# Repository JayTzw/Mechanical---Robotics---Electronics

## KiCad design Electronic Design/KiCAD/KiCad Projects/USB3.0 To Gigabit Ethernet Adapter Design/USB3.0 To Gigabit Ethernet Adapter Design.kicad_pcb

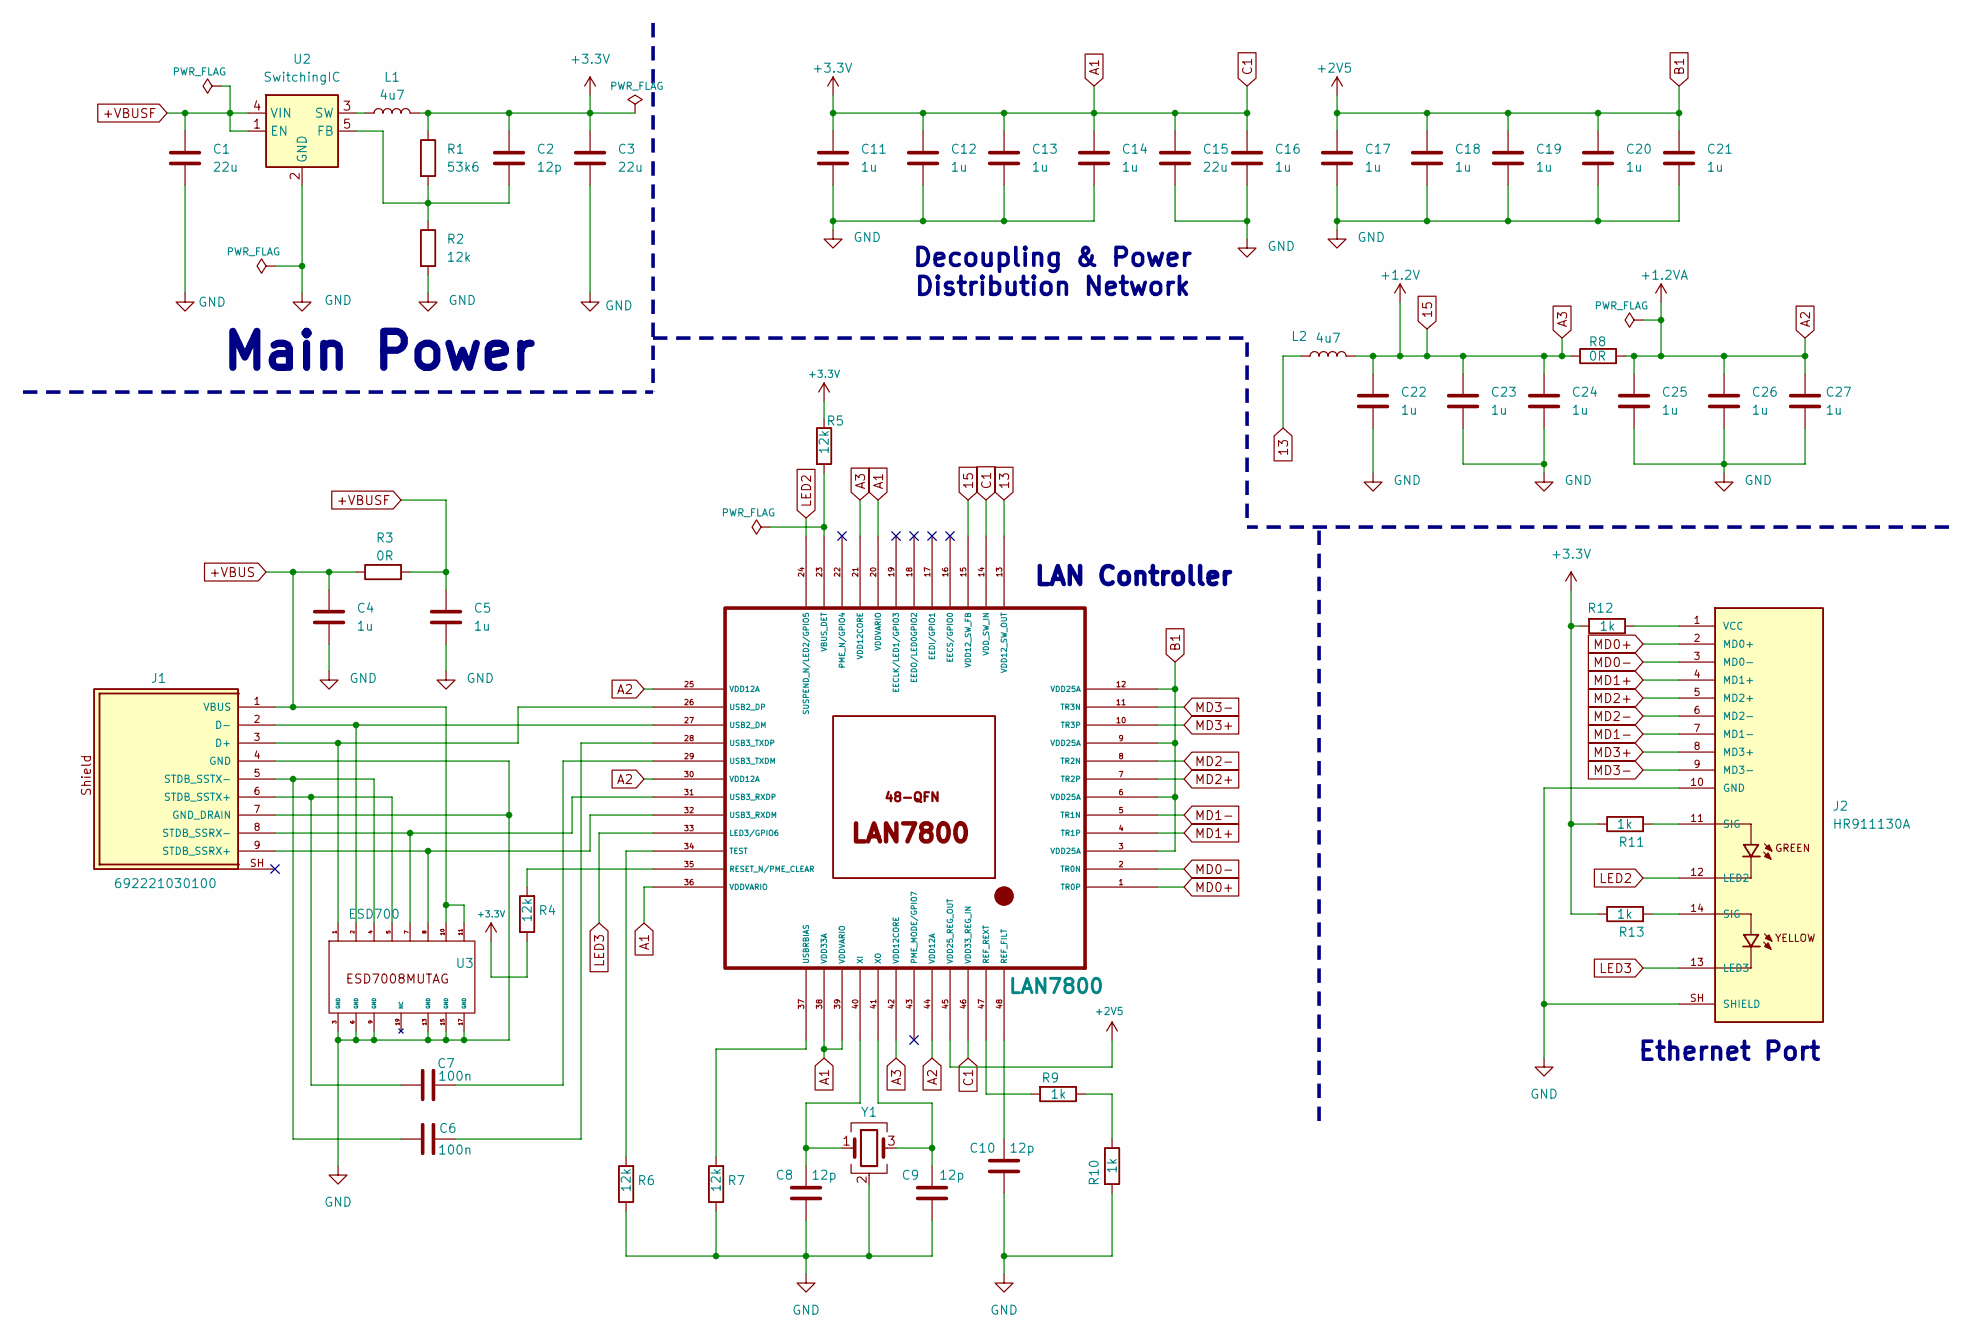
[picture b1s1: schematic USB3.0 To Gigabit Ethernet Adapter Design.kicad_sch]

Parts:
C1, C3, C15: 22u; C_0402_1005Metric
C2, C8, C9, C10: 12p; C_0402_1005Metric
C4, C5, C11, C12, C13, C14, C16, C17, C18, C19, C20, C21, C22, C23, C24, C25, C26, C27: 1u; C_0402_1005Metric
C6, C7: 100n; C_0402_1005Metric
J1: 692221030100
J2: HR911130A; HANRUN_HR911130A; PARTREV A
L1, L2: 4u7; C_0402_1005Metric
R1: 53k6; R_0402_1005Metric
R2, R4, R5, R6, R7: 12k; R_0402_1005Metric
R3, R8: 0R; R_0402_1005Metric
R9, R10, R11, R12, R13: 1k; R_0402_1005Metric
U1: LAN7800; QFN-48-1EP_7x7mm_P0.5mm_EP5.7x5.7mm_ThermalVias
U2: SwitchingIC; SOT-23-5
U3: ESD700; DIO_MG2040MUTAG
Y1: Crystal_GND24; Crystal_SMD_SeikoEpson_FA238-4Pin_3.2x2.5mm

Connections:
13: L2.1, U1.13 (VDD12_SW_OUT)
15: C22.1, C23.1, C24.1, L2.2, R8.1, U1.15 (VDD12_SW_FB), U1.21 (VDD12CORE), U1.42 (VDD12CORE)
+VBUS: C4.1, J1.1 (VBUS), R3.1, U3.10, U3.11
+VBUSF: C1.1, C5.1, R3.2, U2.1 (EN), U2.4 (VIN)
A1: C2.1, C3.1, C11.1, C12.1, C13.1, C14.1, C15.1, C16.1, L1.2, R1.1, R4.1, R5.1, R11.1, R12.2, R13.1, U1.14 (VDD_SW_IN), U1.20 (VDDVARIO), U1.36 (VDDVARIO), U1.38 (VDD33A), U1.39 (VDDVARIO), U1.46 (VDD33_REG_IN)
A2: C25.1, C26.1, C27.1, R8.2, U1.25 (VDD12A), U1.30 (VDD12A), U1.44 (VDD12A)
B1: C17.1, C18.1, C19.1, C20.1, C21.1, U1.3 (VDD25A), U1.6 (VDD25A), U1.9 (VDD25A), U1.12 (VDD25A), U1.45 (VDD25_REG_OUT)
GND: C1.2, C3.2, C4.2, C5.2, C8.1, C9.1, C10.1, C11.2, C12.2, C13.2, C14.2, C15.2, C16.2, C17.2, C18.2, C19.2, C20.2, C21.2, C22.2, C23.2, C24.2, C25.2, C26.2, C27.2, J1.4 (GND), J1.7 (GND_DRAIN), J2.10 (GND), J2.S2 (SHIELD), J2.SH (SHIELD), R2.2, R6.1, R7.1, R10.2, U2.2 (GND), U3.3 (GND), U3.6 (GND), U3.9 (GND), U3.13 (GND), U3.15 (GND), U3.17 (GND), Y1.2 (G), Y1.4 (G)
LED2: J2.12 (LED2), U1.24 (SUSPEND_N/LED2/GPIO5)
LED3: J2.13 (LED3), U1.33 (LED3/GPIO6)
MD0+: J2.2 (MD0+), U1.1 (TR0P)
MD0-: J2.3 (MD0-), U1.2 (TR0N)
MD1+: J2.4 (MD1+), U1.4 (TR1P)
MD1-: J2.7 (MD1-), U1.5 (TR1N)
MD2+: J2.5 (MD2+), U1.7 (TR2P)
MD2-: J2.6 (MD2-), U1.8 (TR2N)
MD3+: J2.8 (MD3+), U1.10 (TR3P)
MD3-: J2.9 (MD3-), U1.11 (TR3N)
unnamed: J1.3 (D+), U1.26 (USB2_DP), U3.1
unnamed: J1.2 (D-), U1.27 (USB2_DM), U3.2
unnamed: J1.9 (STDB_SSRX+), U1.32 (USB3_RXDM), U3.8
unnamed: J1.8 (STDB_SSRX-), U1.31 (USB3_RXDP), U3.7
unnamed: C7.1, J1.6 (STDB_SSTX+), U3.5
unnamed: C6.1, J1.5 (STDB_SSTX-), U3.4
unnamed: J2.11 (SIG), R11.2
unnamed: J2.14 (SIG), R13.2
unnamed: J2.1 (VCC), R12.1
unnamed: R9.1, R10.1
unnamed: C10.2, U1.48 (REF_FILT)
unnamed: R9.2, U1.47 (REF_REXT)
unnamed: R4.2, U1.35 (RESET_N/PME_CLEAR)
unnamed: R6.2, U1.34 (TEST)
unnamed: C7.2, U1.29 (USB3_TXDM)
unnamed: C6.2, U1.28 (USB3_TXDP)
unnamed: R7.2, U1.37 (USBRBIAS)
unnamed: R5.2, U1.23 (VBUS_DET)
unnamed: C8.2, U1.40 (XI), Y1.1
unnamed: C9.2, U1.41 (XO), Y1.3
unnamed: C2.2, R1.2, R2.1, U2.5 (FB)
unnamed: L1.1, U2.3 (SW)

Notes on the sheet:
Decoupling & Power Distribution Network
Main Power
LAN Controller
Ethernet Port

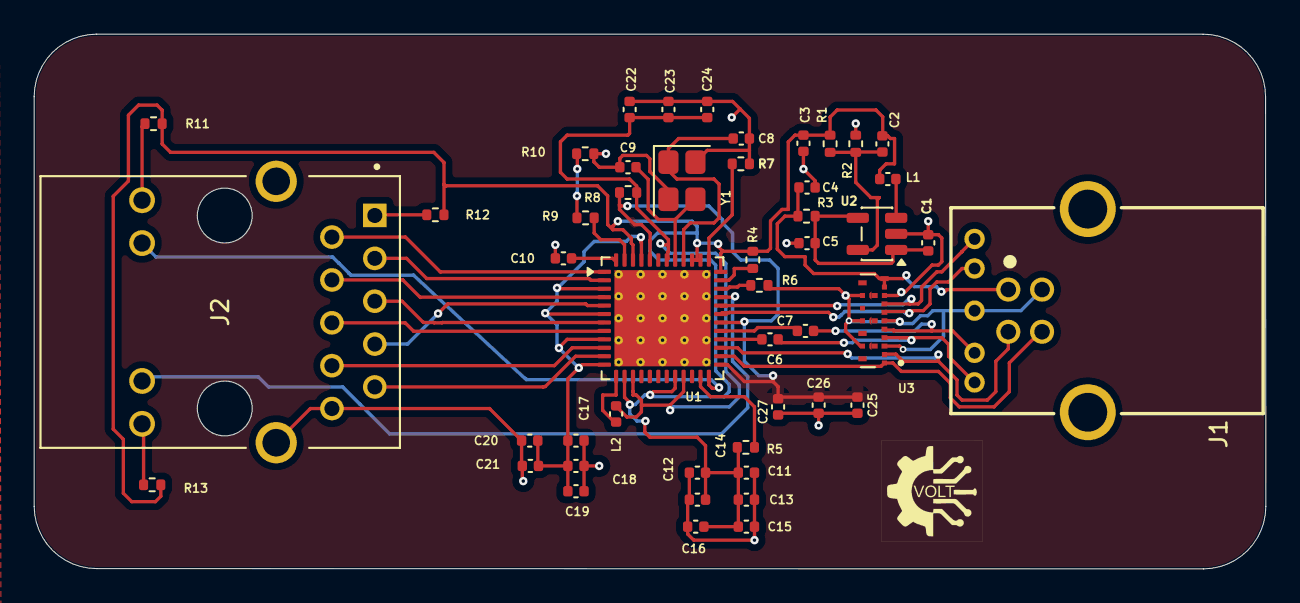
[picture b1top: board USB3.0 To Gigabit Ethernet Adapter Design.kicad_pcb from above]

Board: 2 copper layers, 73.0 x 31.7 mm, 48 parts (0 on the bottom side), 40 nets.

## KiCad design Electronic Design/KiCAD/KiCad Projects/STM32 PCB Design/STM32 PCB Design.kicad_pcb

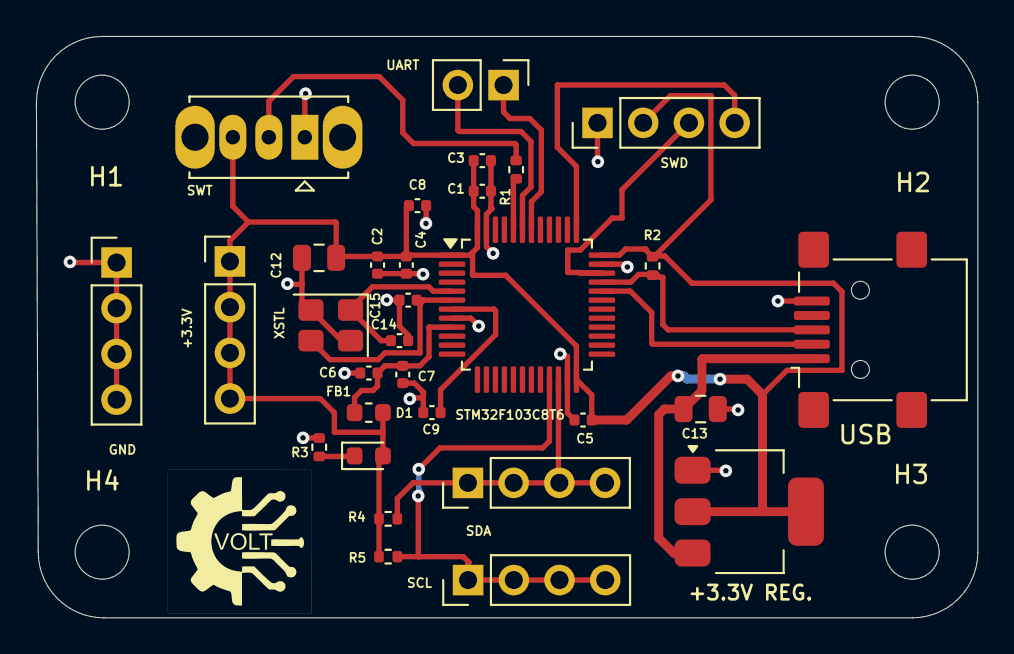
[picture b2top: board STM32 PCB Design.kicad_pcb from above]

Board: 2 copper layers, 52.3 x 32.3 mm, 35 parts (0 on the bottom side), 18 nets.

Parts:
+3.3V: Conn_01x04; PinHeader_1x04_P2.54mm_Vertical
+3.3V REG.: AMS1117-3.3; SOT-223-3_TabPin2
C1, C2, C3, C4, C5: 100n; C_0402_1005Metric
C6: 10n; C_0402_1005Metric
C7, C8: 1u; C_0402_1005Metric
C9: 10u; C_0402_1005Metric
C12, C13: 22u; C_0805_2012Metric
C14, C15: 10p; C_0402_1005Metric
D1: RED; LED_0603_1608Metric
FB1: 120R; L_0603_1608Metric
GND: Conn_01x04; PinHeader_1x04_P2.54mm_Vertical
H1, H2, H3, H4: MountingHole; MountingHole_3mm
R1: 10k; R_0402_1005Metric
R2, R3, R4, R5: 1.5k; R_0402_1005Metric
SCL: Conn_01x04; PinHeader_1x04_P2.54mm_Vertical
SDA: Conn_01x04; PinHeader_1x04_P2.54mm_Vertical
STM32F103C8T6: STM32F103C8T6; LQFP-48_7x7mm_P0.5mm
SWD: Conn_01x04; PinHeader_1x04_P2.54mm_Vertical
SWT: SW_Wuerth_450301014042; SW_Slide_SPDT_Straight_CK_OS102011MS2Q
UART: Conn_01x02; PinHeader_1x02_P2.54mm_Vertical
USB: USB_B_Micro; USB_Mini-B_Lumberg_2486_01_Horizontal
XSTL: Crystal_GND24; Crystal_SMD_3225-4Pin_3.2x2.5mm

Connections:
+3.3V: +3.3V.1, +3.3V.2, +3.3V.3, +3.3V.4, +3.3V REG..2 (VO), C1.1, C2.1, C3.1, C4.1, C5.1, C8.1, C12.1, D1.2 (A), FB1.2, R2.2, R4.2, R5.2, STM32F103C8T6.1 (VBAT), STM32F103C8T6.24 (VDD), STM32F103C8T6.36 (VDD), STM32F103C8T6.48 (VDD), SWD.2, SWT.3 (C)
+3.3VA: C6.1, C7.1, FB1.1, STM32F103C8T6.9 (VDDA)
/BOOT0: R1.2, STM32F103C8T6.44 (BOOT0)
/HSE_IN: C14.1, STM32F103C8T6.5 (PD0), XSTL.1
/HSE_OUT: C15.1, STM32F103C8T6.6 (PD1), XSTL.3
/I2C2_SCL: R5.1, SCL.1, SCL.2, SCL.3, SCL.4, STM32F103C8T6.21 (PB10)
/I2C2_SDA: R4.1, SDA.1, SDA.2, SDA.3, SDA.4, STM32F103C8T6.22 (PB11)
/NRST: C9.2, STM32F103C8T6.7 (NRST)
/PWR_LED_K: D1.1 (K), R3.2
/SWCLK: STM32F103C8T6.37 (PA14), SWD.4
/SWDIO: STM32F103C8T6.34 (PA13), SWD.3
/SW_BOOT0: R1.1, SWT.2 (B)
/USART1_RX: STM32F103C8T6.43 (PB7), UART.2
/USART1_TX: STM32F103C8T6.42 (PB6), UART.1
/USB_D+: R2.1, STM32F103C8T6.33 (PA12), USB.3 (D+)
/USB_D-: STM32F103C8T6.32 (PA11), USB.2 (D-)
GND: +3.3V REG..1 (GND), C1.2, C2.2, C3.2, C4.2, C5.2, C6.2, C7.2, C8.2, C9.1, C12.2, C13.2, C14.2, C15.2, GND.1, GND.2, GND.3, GND.4, R3.1, STM32F103C8T6.8 (VSSA), STM32F103C8T6.23 (VSS), STM32F103C8T6.35 (VSS), STM32F103C8T6.47 (VSS), SWD.1, SWT.1 (A), USB.5 (GND), XSTL.2 (G), XSTL.4 (G)
VBUS: +3.3V REG..3 (VI), C13.1, USB.1 (VBUS)

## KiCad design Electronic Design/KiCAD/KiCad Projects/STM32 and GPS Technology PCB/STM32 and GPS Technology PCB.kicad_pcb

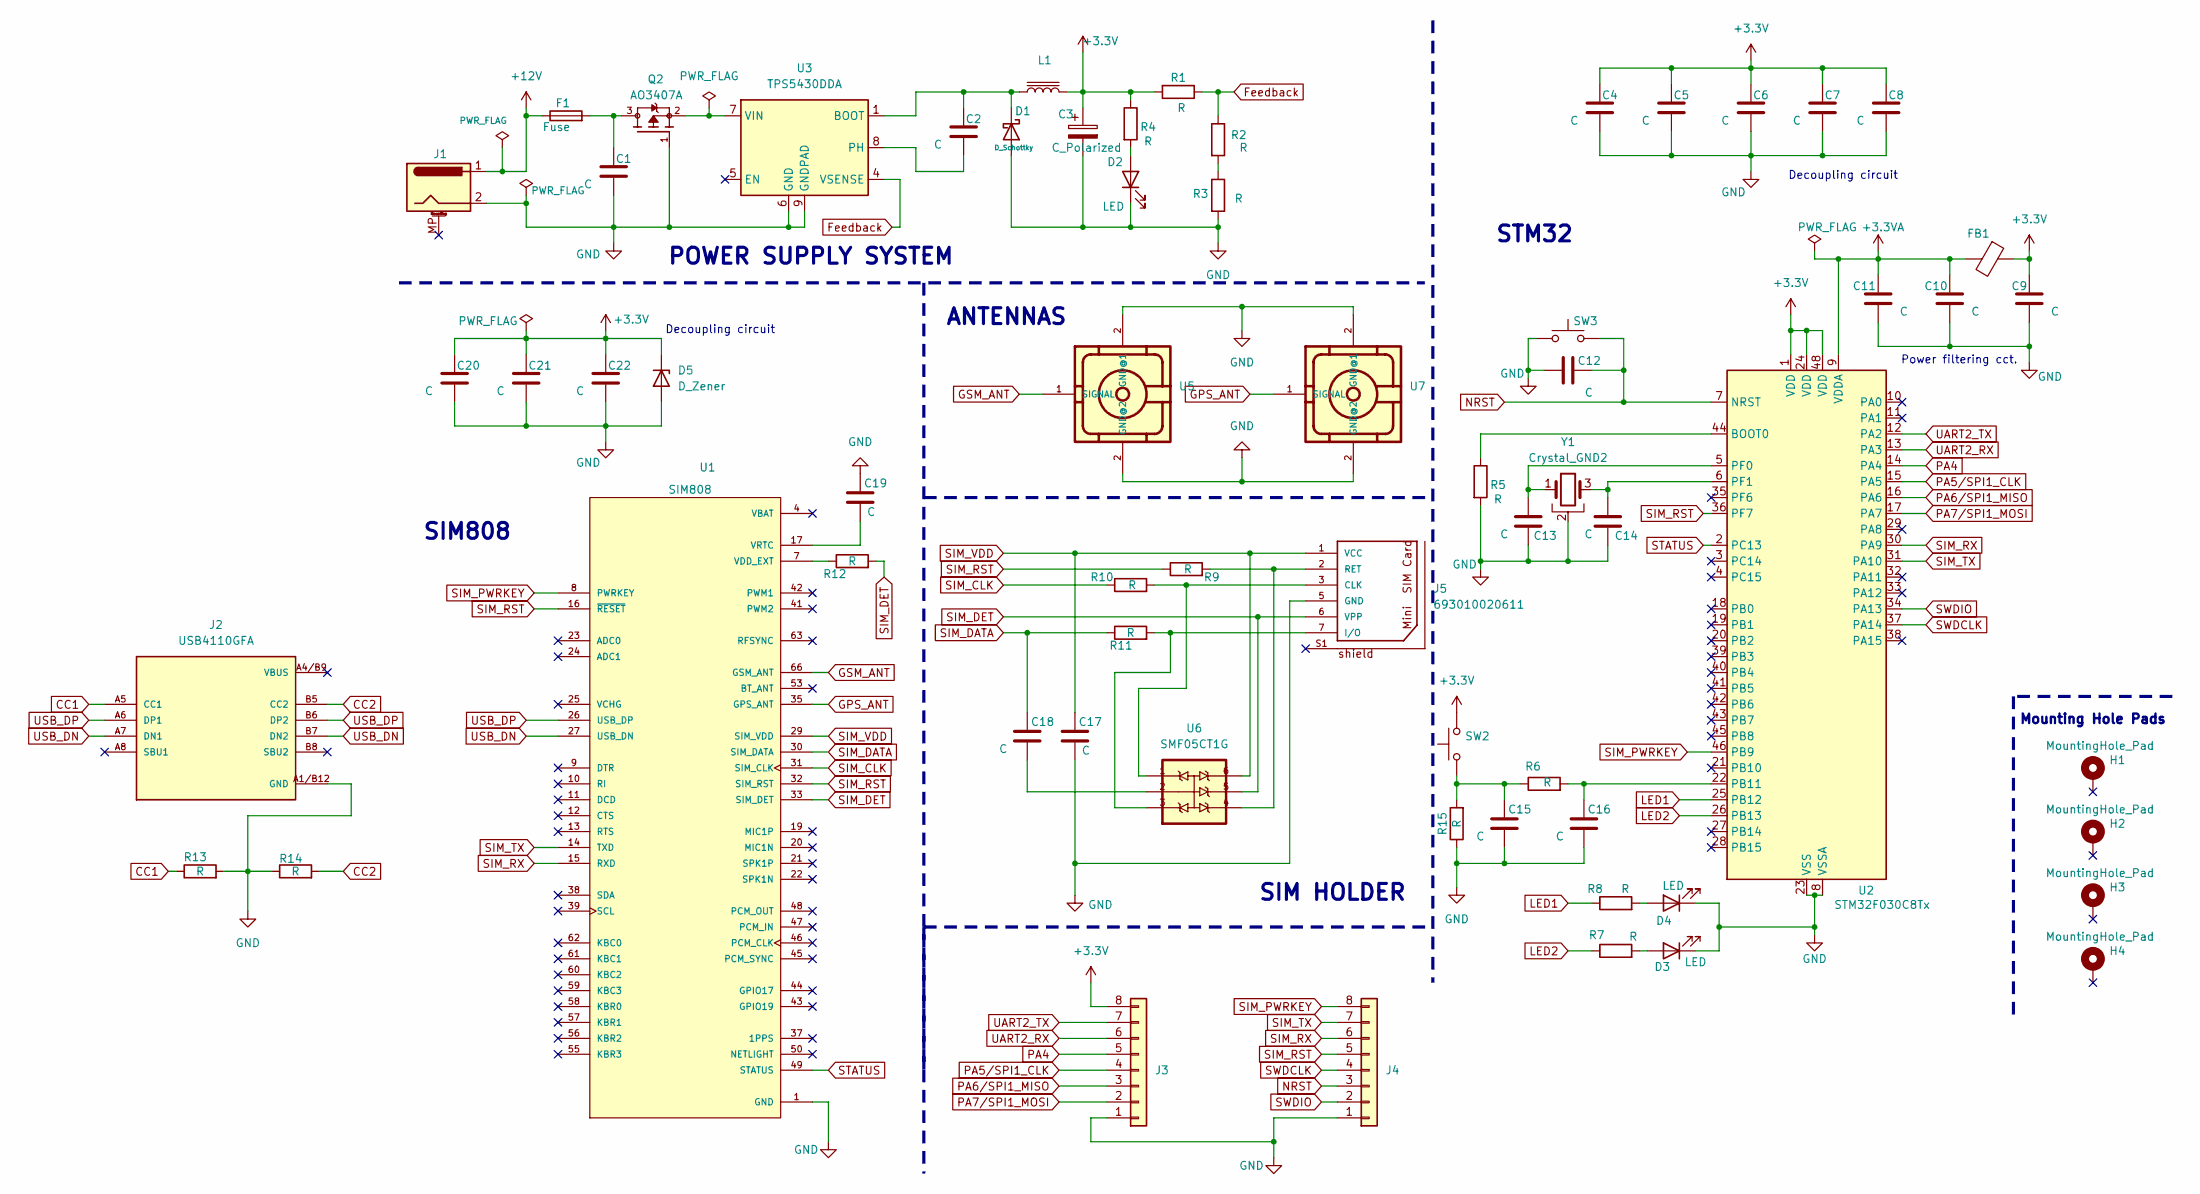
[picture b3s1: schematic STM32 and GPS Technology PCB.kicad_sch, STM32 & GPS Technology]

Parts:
C1, C2, C4, C5, C6, C7, C8, C9, C10, C11, C12, C13, C14, C15, C16, C17, C18, C19, C20, C21, C22: C
C3: C_Polarized
D1: D_Schottky
D2, D3, D4: LED
D5: D_Zener
F1: Fuse
FB1: FerriteBead
H1, H2, H3, H4: MountingHole_Pad
J1: Barrel_Jack_MountingPin; BarrelJack_GCT_DCJ200-10-A_Horizontal
J2: USB4110GFA; USB_C_Receptacle_GCT_USB4110
J3, J4: Conn_01x08
J5: 693010020611
L1: L_Iron
Q2: AO3407A; SOT-23-3; PARTREV 5
R1, R2, R3, R4, R5, R6, R7, R8, R9, R10, R11, R12, R13, R14, R15: R
SW2, SW3: SW_Push
U1: SIM808; XCVR_SIM808; PARTREV 1.03
U2: STM32F030C8Tx; LQFP-48_7x7mm_P0.5mm
U3: TPS5430DDA; TI_SO-PowerPAD-8_ThermalVias
U5, U7: U.FL-R-SMT-1_60_; U.FL_Hirose_U.FL-R-SMT-1_Vertical
U6: SMF05CT1G; SOT-363_SC-70-6
Y1: Crystal_GND2

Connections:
+3.3V: C3.1, C4.1, C5.1, C6.1, C7.1, C8.1, C9.1, C20.1, C21.1, C22.1, D5.1 (K), FB1.1, J3.8, L1.2, R1.2, R4.1, SW2.2, U2.1 (VDD), U2.24 (VDD), U2.48 (VDD); also elsewhere on the board
+3.3VA: C10.1, C11.1, FB1.2, U2.9 (VDDA); also elsewhere on the board
+12V: F1.1, J1.1
CC1: J2.A5 (CC1), R13.1
CC2: J2.B5 (CC2), R14.2
Feedback: R1.1, R2.1, U3.4 (VSENSE)
GND: C1.2, C3.2, C4.2, C5.2, C6.2, C7.2, C8.2, C9.2, C10.2, C11.2, C12.1, C13.1, C14.1, C15.1, C16.1, C17.1, C19.2, C20.2, C21.2, C22.2, D1.2 (A), D2.1 (K), D3.1 (K), D4.1 (K), D5.2 (A), J1.2, J2.A1, J2.A1/B12 (GND), J2.B1/A12 (GND), J2.B12, J2.GND, J2.S1 (GND), J2.S2 (GND), J2.S3 (GND), J2.S4 (GND), J3.1, J4.1, J5.5 (GND), Q2.1, R3.2, R5.2, R13.2, R14.1, R15.1, SW3.1, U1.1 (GND), U1.2 (GND), U1.3 (GND), U1.18 (GND), U1.28 (GND), U1.34 (GND), U1.36 (GND), U1.40 (GND), U1.51 (GND), U1.52 (GND), U1.54 (GND), U1.64 (GND), U1.65 (GND), U1.67 (GND), U1.68 (GND), U2.8 (VSSA), U2.23 (VSS), U2.47 (VSS), U3.6 (GND), U3.9 (GNDPAD), U5.2 (GND@1), U7.2 (GND@1), Y1.2; also elsewhere on the board
LED1: R8.1, U2.25 (PB12); also elsewhere on the board
LED2: R7.1, U2.26 (PB13); also elsewhere on the board
NRST: C12.2, J4.3, SW3.2, U2.7 (NRST); also elsewhere on the board
unnamed: C1.1, F1.2, Q2.3
unnamed: C15.2, R6.1, R15.2, SW2.1
unnamed: C18.1, U6.2
unnamed: C2.1, D1.1 (K), L1.1, U3.1 (BOOT)
unnamed: D2.2 (A), R4.2
unnamed: D3.2 (A), R7.2
unnamed: D4.2 (A), R8.2
unnamed 19: J5.3 (CLK), R10.2, U6.1; also elsewhere on the board
unnamed 20: J5.7 (I/O), R11.2, U6.3; also elsewhere on the board
unnamed: J5.S1, J5.S2, J5.S3, J5.S4
unnamed 22: J5.2 (RET), R9.2, U6.4; also elsewhere on the board
unnamed: R2.2, R3.1
unnamed: U1.4 (VBAT), U1.5 (VBAT), U1.6 (VBAT)
unnamed: U1.35 (GPS_ANT), U7.1 (SIGNAL)
unnamed: U1.49 (STATUS), U2.2 (PC13)
unnamed: U1.66 (GSM_ANT), U5.1 (SIGNAL)
unnamed 28: R12.1, U1.7 (VDD_EXT); also elsewhere on the board
unnamed 29: C19.1, U1.17 (VRTC); also elsewhere on the board
unnamed 30: R5.1, U2.44 (BOOT0); also elsewhere on the board
unnamed 31: C16.2, R6.2, U2.22 (PB11); also elsewhere on the board
unnamed 32: C13.2, U2.5 (PF0), Y1.1; also elsewhere on the board
unnamed 33: C14.2, U2.6 (PF1), Y1.3; also elsewhere on the board
unnamed: C2.2, U3.8 (PH)
unnamed: Q2.2, U3.7 (VIN)
PA4: J3.5, U2.14 (PA4); also elsewhere on the board
PA5/SPI1_CLK: J3.4, U2.15 (PA5); also elsewhere on the board
PA6/SPI1_MISO: J3.3, U2.16 (PA6); also elsewhere on the board
PA7/SPI1_MOSI: J3.2, U2.17 (PA7); also elsewhere on the board
SIM_CLK: R10.1, U1.31 (SIM_CLK); also elsewhere on the board
SIM_DATA: C18.2, R11.1, U1.30 (SIM_DATA); also elsewhere on the board
SIM_DET: J5.6 (VPP), R12.2, U1.33 (SIM_DET), U6.5; also elsewhere on the board
SIM_PWRKEY: J4.8, U1.8 (PWRKEY), U2.46 (PB9); also elsewhere on the board
SIM_RST: J4.5, R9.1, U1.16 (~RESET), U1.32 (SIM_RST), U2.36 (PF7); also elsewhere on the board
SIM_RX: J4.6, U1.15 (RXD), U2.30 (PA9); also elsewhere on the board
SIM_TX: J4.7, U1.14 (TXD), U2.31 (PA10); also elsewhere on the board
SIM_VDD: C17.2, J5.1 (VCC), U1.29 (SIM_VDD), U6.6; also elsewhere on the board
SWDCLK: J4.4, U2.37 (PA14); also elsewhere on the board
SWDIO: J4.2, U2.34 (PA13); also elsewhere on the board
UART2_RX: J3.6, U2.13 (PA3); also elsewhere on the board
UART2_TX: J3.7, U2.12 (PA2); also elsewhere on the board
USB_DN: J2.A7 (DN1), J2.B7 (DN2), U1.27 (USB_DN); also elsewhere on the board
USB_DP: J2.A6 (DP1), J2.B6 (DP2), U1.26 (USB_DP); also elsewhere on the board

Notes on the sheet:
SIM HOLDER
ANTENNAS
Power filtering cct.
SIM808
Mounting Hole Pads
Decoupling circuit
POWER SUPPLY SYSTEM
STM32

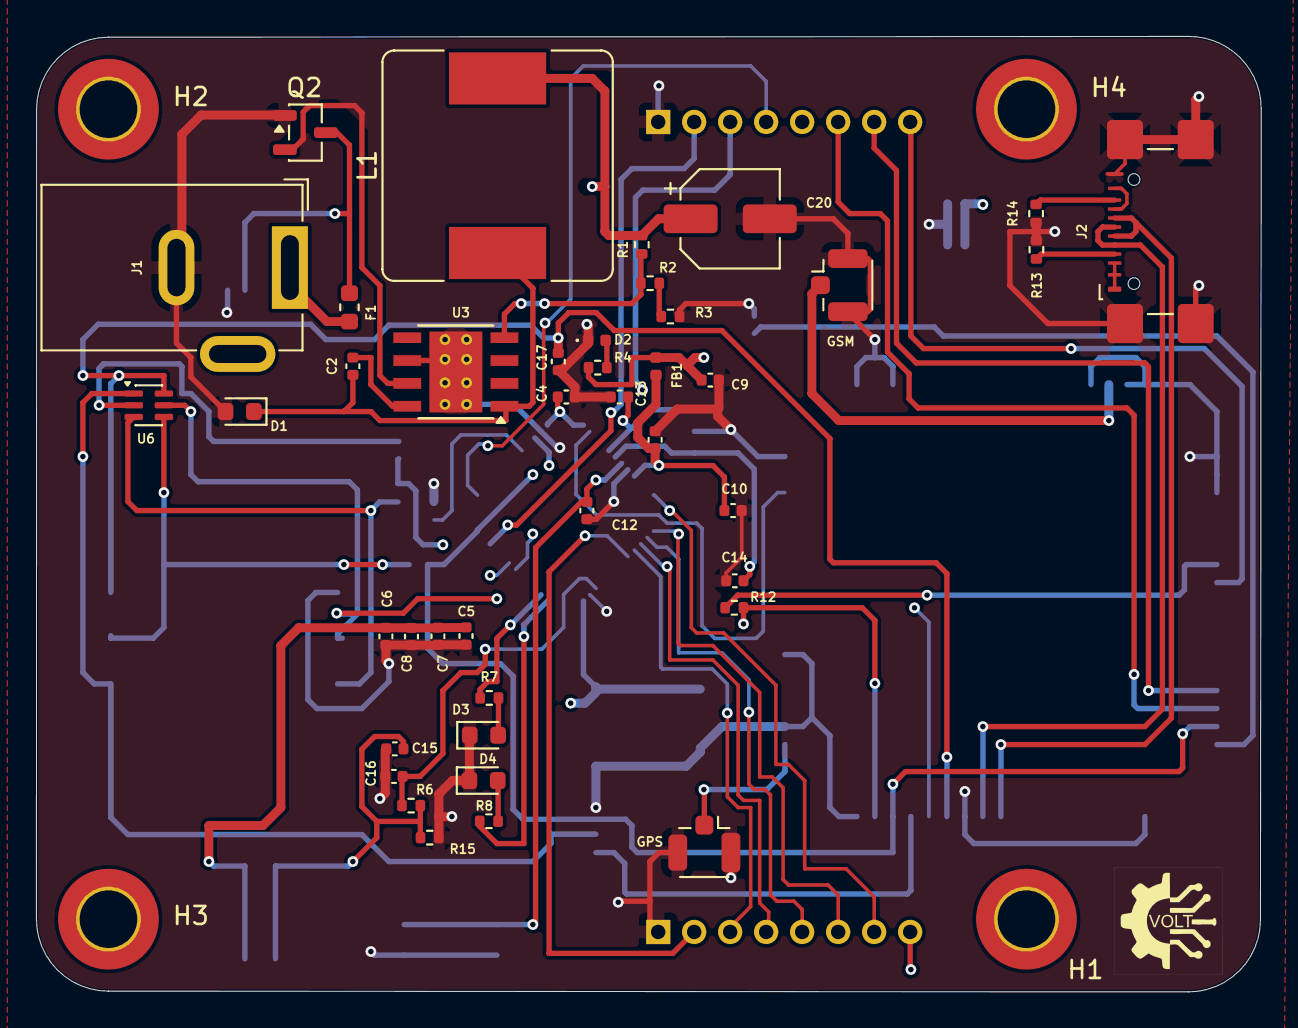
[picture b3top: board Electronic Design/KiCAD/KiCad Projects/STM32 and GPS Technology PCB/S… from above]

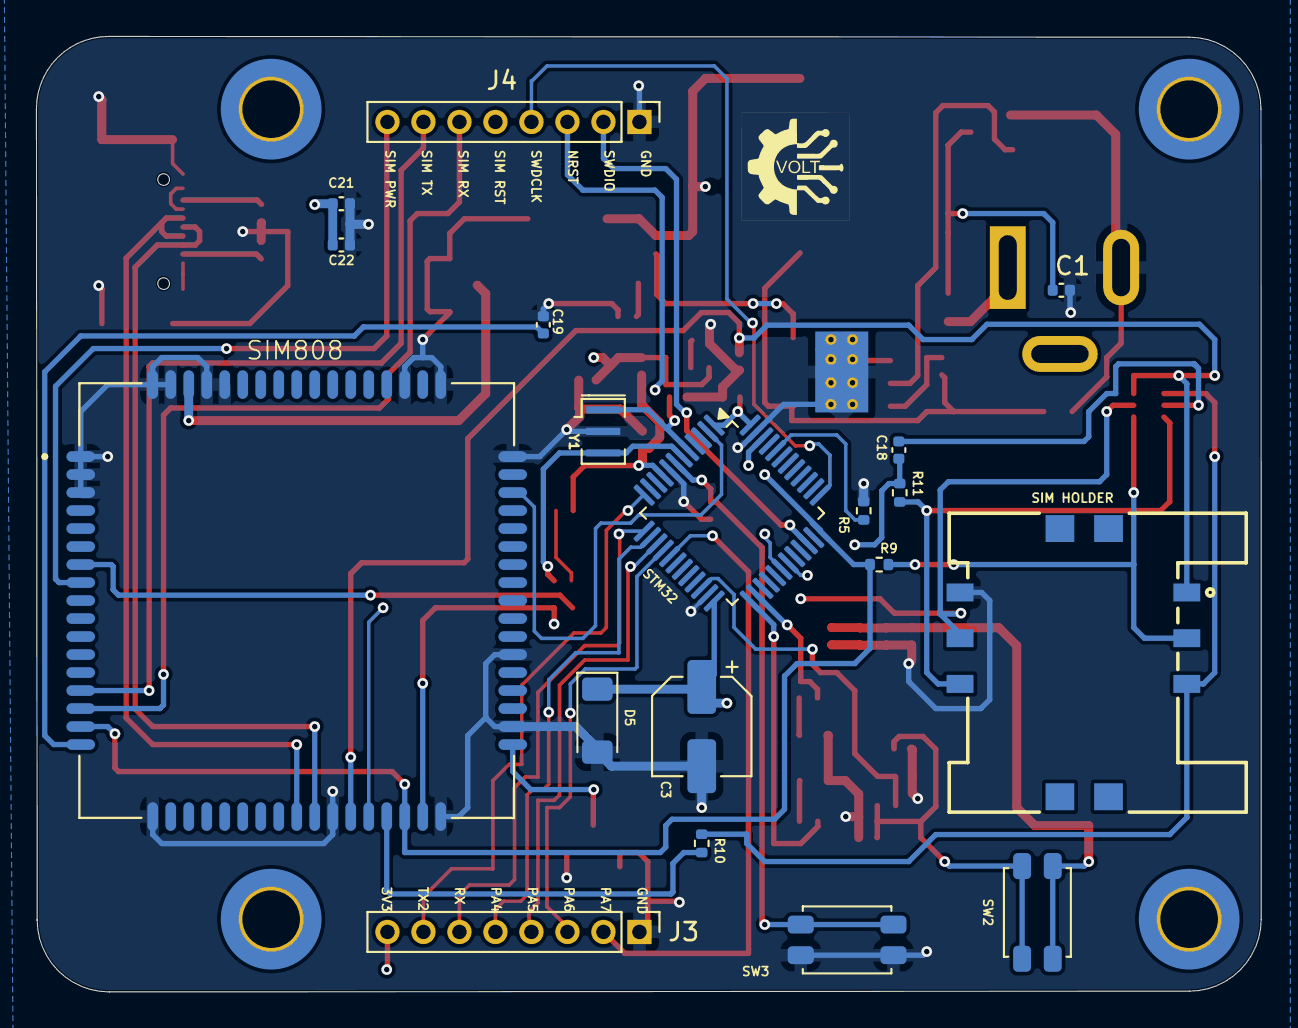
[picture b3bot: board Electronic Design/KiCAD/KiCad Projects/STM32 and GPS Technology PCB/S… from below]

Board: 4 copper layers, 68.0 x 53.1 mm, 64 parts (19 on the bottom side), 50 nets.

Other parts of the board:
GPS: U.FL-R-SMT-1_60_; U.FL_Hirose_U.FL-R-SMT-1_Vertical
GSM: U.FL-R-SMT-1_60_; U.FL_Hirose_U.FL-R-SMT-1_Vertical
SIM808: SIM808; XCVR_SIM808
SIM HOLDER: 693010020611
STM32: STM32F030C8Tx; LQFP-48_7x7mm_P0.5mm

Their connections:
+3.3V: STM32.1 (VDD), STM32.24 (VDD), STM32.48 (VDD); also elsewhere on the board
+3.3VA: STM32.9 (VDDA); also elsewhere on the board
GND: GPS.2 (GND@1), GSM.2 (GND@1), SIM808.1 (GND), SIM808.2 (GND), SIM808.3 (GND), SIM808.18 (GND), SIM808.28 (GND), SIM808.34 (GND), SIM808.36 (GND), SIM808.40 (GND), SIM808.51 (GND), SIM808.52 (GND), SIM808.54 (GND), SIM808.64 (GND), SIM808.65 (GND), SIM808.67 (GND), SIM808.68 (GND), SIM HOLDER.5 (GND), STM32.8 (VSSA), STM32.23 (VSS), STM32.47 (VSS); also elsewhere on the board
GPS_ANT: GPS.1 (SIGNAL), SIM808.35 (GPS_ANT)
GSM_ANT: GSM.1 (SIGNAL), SIM808.66 (GSM_ANT)
LED1: STM32.25 (PB12); also elsewhere on the board
LED2: STM32.26 (PB13); also elsewhere on the board
NRST: STM32.7 (NRST); also elsewhere on the board
unnamed 19: SIM HOLDER.3 (CLK); also elsewhere on the board
unnamed 20: SIM HOLDER.7 (I/O); also elsewhere on the board
unnamed 22: SIM HOLDER.2 (RET); also elsewhere on the board
unnamed 28: SIM808.7 (VDD_EXT); also elsewhere on the board
unnamed 29: SIM808.17 (VRTC); also elsewhere on the board
unnamed 30: STM32.44 (BOOT0); also elsewhere on the board
unnamed 31: STM32.22 (PB11); also elsewhere on the board
unnamed 32: STM32.5 (PF0); also elsewhere on the board
unnamed 33: STM32.6 (PF1); also elsewhere on the board
PA4: STM32.14 (PA4); also elsewhere on the board
PA5/SPI1_CLK: STM32.15 (PA5); also elsewhere on the board
PA6/SPI1_MISO: STM32.16 (PA6); also elsewhere on the board
PA7/SPI1_MOSI: STM32.17 (PA7); also elsewhere on the board
SIM_CLK: SIM808.31 (SIM_CLK); also elsewhere on the board
SIM_DATA: SIM808.30 (SIM_DATA); also elsewhere on the board
SIM_DET: SIM808.33 (SIM_DET), SIM HOLDER.6 (VPP); also elsewhere on the board
SIM_PWRKEY: SIM808.8 (PWRKEY), STM32.46 (PB9); also elsewhere on the board
SIM_RST: SIM808.16 (~RESET), SIM808.32 (SIM_RST), STM32.36 (PF7); also elsewhere on the board
SIM_RX: SIM808.15 (RXD), STM32.30 (PA9); also elsewhere on the board
SIM_TX: SIM808.14 (TXD), STM32.31 (PA10); also elsewhere on the board
SIM_VDD: SIM808.29 (SIM_VDD), SIM HOLDER.1 (VCC); also elsewhere on the board
STATUS: SIM808.49 (STATUS), STM32.2 (PC13)
SWDCLK: STM32.37 (PA14); also elsewhere on the board
SWDIO: STM32.34 (PA13); also elsewhere on the board
UART2_RX: STM32.13 (PA3); also elsewhere on the board
UART2_TX: STM32.12 (PA2); also elsewhere on the board
USB_DN: SIM808.27 (USB_DN); also elsewhere on the board
USB_DP: SIM808.26 (USB_DP); also elsewhere on the board

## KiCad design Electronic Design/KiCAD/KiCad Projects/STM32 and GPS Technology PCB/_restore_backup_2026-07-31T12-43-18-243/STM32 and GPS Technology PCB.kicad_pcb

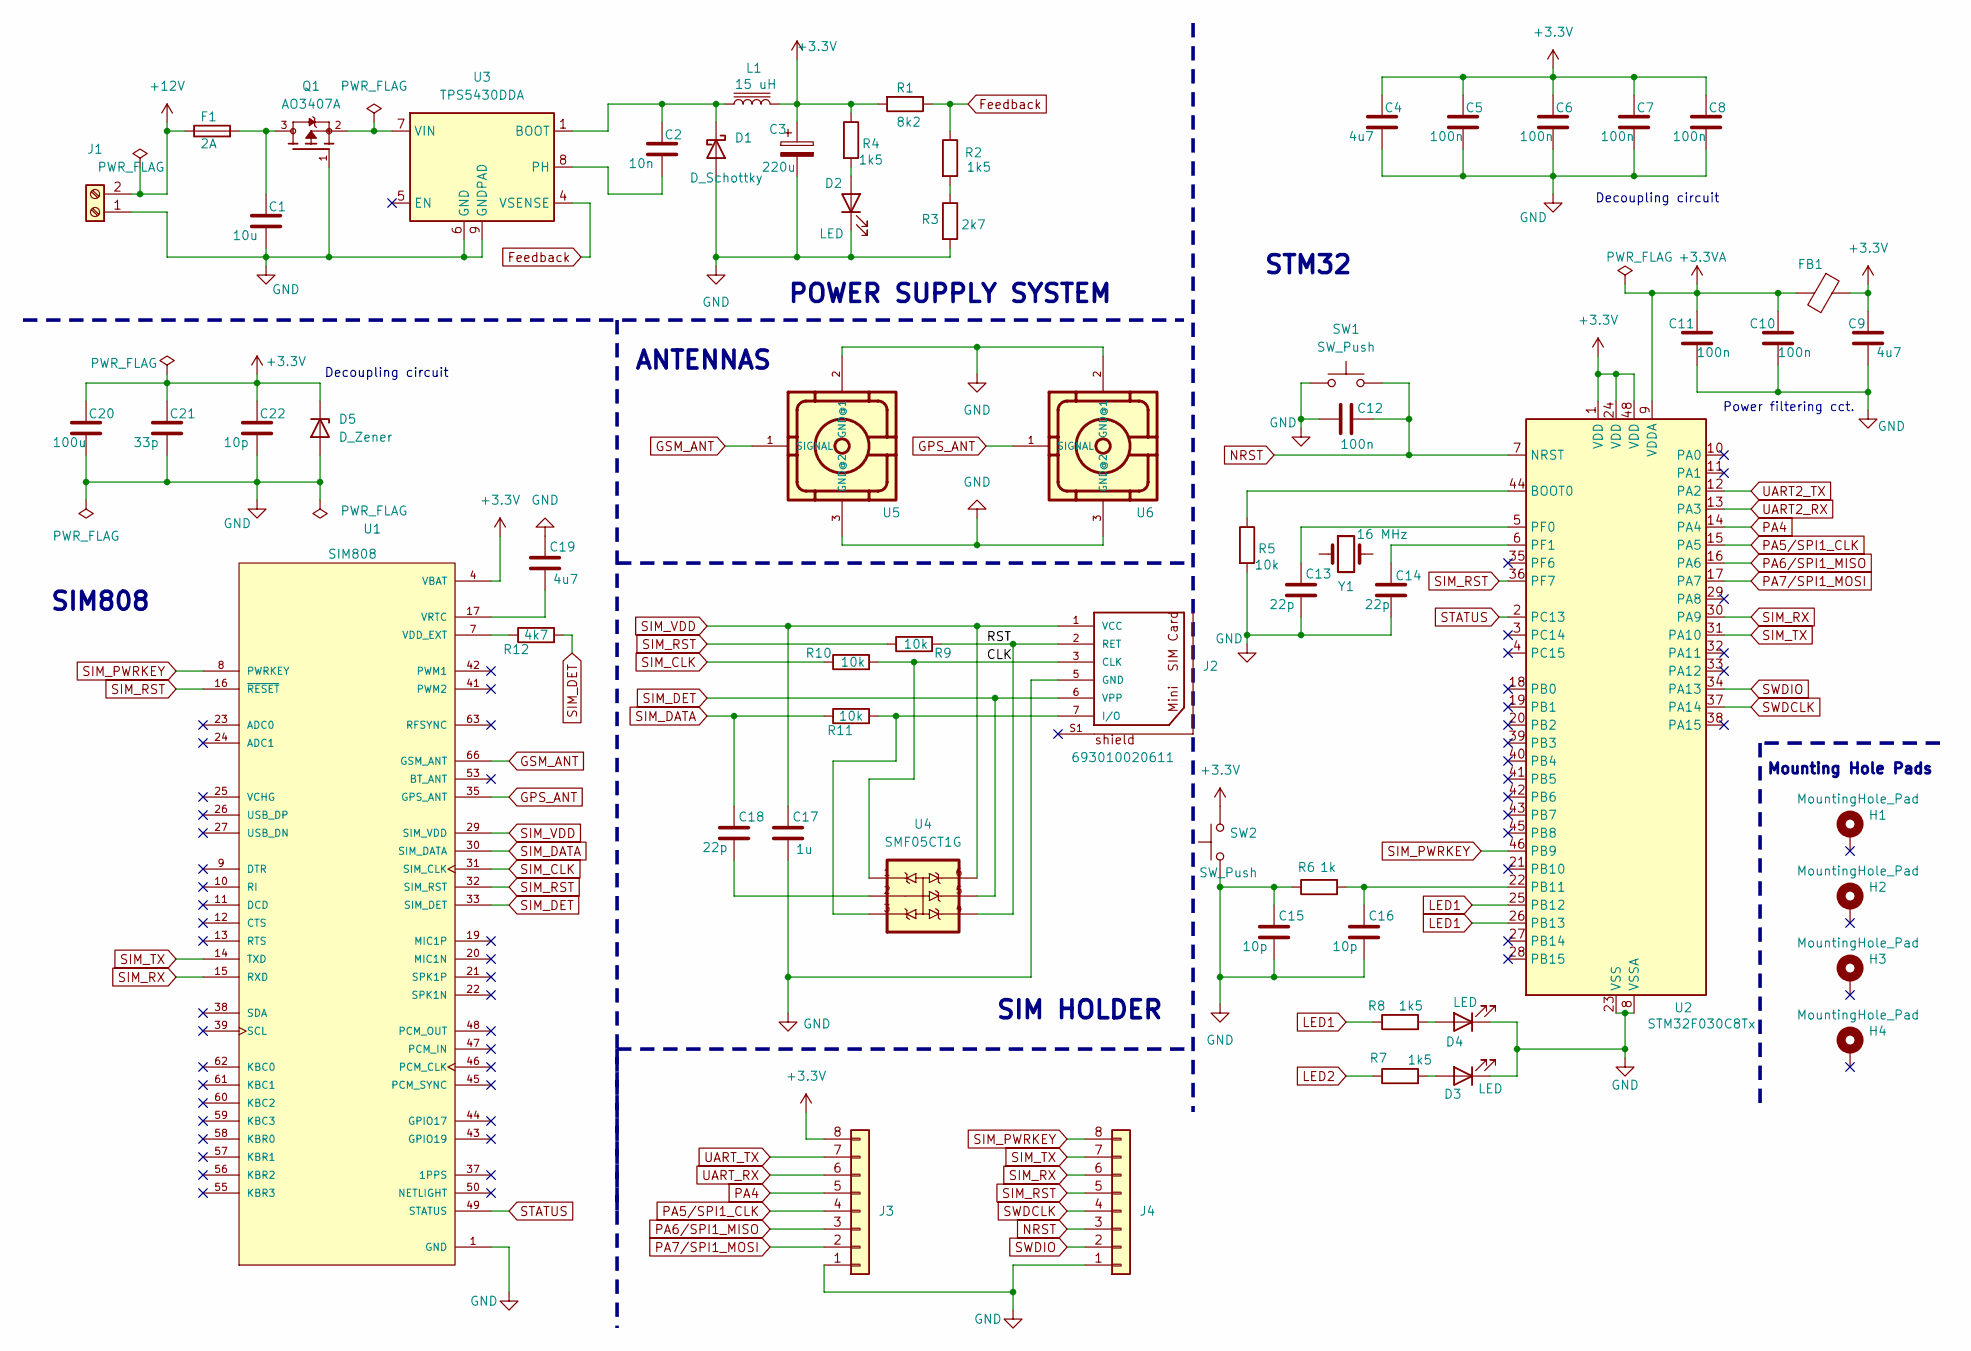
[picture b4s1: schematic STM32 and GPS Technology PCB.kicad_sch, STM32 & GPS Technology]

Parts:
C1: 10u; C_0402_1005Metric
C2: 10n; C_0201_0603Metric
C3: 220u; CP_Elec_5x3
C4, C9: 4u7; C_0402_1005Metric
C5, C6, C7, C8, C10, C11, C12: 100n; C_0201_0603Metric
C13, C14, C18: 22p; C_0201_0603Metric
C15, C16, C22: 10p; C_0201_0603Metric
C17: 1u; C_0402_1005Metric
C19: 4u7; C_0201_0603Metric
C20: 100u; C_0201_0603Metric
C21: 33p; C_0201_0603Metric
D1: D_Schottky; D_0603_1608Metric
D2: LED; LED_0402_1005Metric
D3, D4: LED; LED_0603_1608Metric
D5: D_Zener; D_0402_1005Metric
F1: 2A; Fuse_0603_1608Metric
FB1: FerriteBead; L_0402_1005Metric
H1, H2, H3, H4: MountingHole_Pad; MountingHole_3.2mm_M3_DIN965_Pad_TopBottom
J1: Screw_Terminal_01x02; TerminalBlock_Phoenix_MKDS-1,5-2_1x02_P5.00mm_Horizontal
J2: 693010020611
J3, J4: Conn_01x08; PinHeader_1x08_P2.00mm_Vertical
L1: 15 uH; L_0402_1005Metric
Q1: AO3407A; SuperSOT-3; PARTREV 5
R1: 8k2; R_0402_1005Metric
R2, R4, R7, R8: 1k5; R_0402_1005Metric
R3: 2k7; R_0402_1005Metric
R5, R9, R10, R11: 10k; R_0402_1005Metric
R6: 1k; R_0402_1005Metric
R12: 4k7; R_0201_0603Metric
SW1, SW2: SW_Push; SW_SPST_B3SL-1002P
U1: SIM808; XCVR_SIM808; PARTREV 1.03
U2: STM32F030C8Tx; LQFP-48_7x7mm_P0.5mm
U3: TPS5430DDA; TI_SO-PowerPAD-8_ThermalVias
U4: SMF05CT1G; SOT65P210X110-6N
U5, U6: U.FL-R-SMT-1_60_; U.FL_Hirose_U.FL-R-SMT-1_Vertical
Y1: 16 MHz; Crystal_SMD_2012-2Pin_2.0x1.2mm

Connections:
+3.3V: C3.1, C4.1, C5.1, C6.1, C7.1, C8.1, C9.1, C20.1, C21.1, C22.1, D5.1 (K), FB1.1, J3.8, L1.2, R1.2, R4.1, SW2.2, U1.4 (VBAT), U1.5 (VBAT), U1.6 (VBAT), U2.1 (VDD), U2.24 (VDD), U2.48 (VDD)
+3.3VA: C10.1, C11.1, FB1.2, U2.9 (VDDA)
+12V: F1.1, J1.2
Feedback: R1.1, R2.1, U3.4 (VSENSE)
GND: C1.2, C3.2, C4.2, C5.2, C6.2, C7.2, C8.2, C9.2, C10.2, C11.2, C12.1, C13.1, C14.1, C15.1, C15.2, C16.1, C17.1, C19.2, C20.2, C21.2, C22.2, D1.2 (A), D2.1 (K), D3.1 (K), D4.1 (K), D5.2 (A), J1.1, J2.5 (GND), J3.1, J4.1, Q1.1, R3.2, R5.2, R6.1, SW1.1, SW2.1, U1.1 (GND), U1.2 (GND), U1.3 (GND), U1.18 (GND), U1.28 (GND), U1.34 (GND), U1.36 (GND), U1.40 (GND), U1.51 (GND), U1.52 (GND), U1.54 (GND), U1.64 (GND), U1.65 (GND), U1.67 (GND), U1.68 (GND), U2.8 (VSSA), U2.23 (VSS), U2.47 (VSS), U3.6 (GND), U3.9 (GNDPAD), U5.2 (GND@1), U5.3 (GND@2), U6.2 (GND@1), U6.3 (GND@2)
GPS_ANT: U1.35 (GPS_ANT), U6.1 (SIGNAL)
GSM_ANT: U1.66 (GSM_ANT), U5.1 (SIGNAL)
LED1: R8.1, U2.25 (PB12), U2.26 (PB13)
LED2: R7.1
NRST: C12.2, J4.3, SW1.2, U2.7 (NRST)
unnamed: C1.1, F1.2, Q1.3
unnamed: C18.1, U4.2
unnamed: C2.1, D1.1 (K), L1.1, U3.1 (BOOT)
unnamed: D2.2 (A), R4.2
unnamed: D3.2 (A), R7.2
unnamed: D4.2 (A), R8.2
unnamed: J2.S1, J2.S2, J2.S3, J2.S4
unnamed: J2.3 (CLK), R10.2, U4.1
unnamed: J2.7 (I/O), R11.2, U4.3
unnamed: J2.2 (RET), R9.2, U4.4
unnamed: R2.2, R3.1
unnamed: R12.1, U1.7 (VDD_EXT)
unnamed: C19.1, U1.17 (VRTC)
unnamed: R5.1, U2.44 (BOOT0)
unnamed: C16.2, R6.2, U2.22 (PB11)
unnamed: C13.2, U2.5 (PF0)
unnamed: C14.2, U2.6 (PF1)
unnamed: C2.2, U3.8 (PH)
unnamed: Q1.2, U3.7 (VIN)
PA4: J3.5, U2.14 (PA4)
PA5/SPI1_CLK: J3.4, U2.15 (PA5)
PA6/SPI1_MISO: J3.3, U2.16 (PA6)
PA7/SPI1_MOSI: J3.2, U2.17 (PA7)
SIM_CLK: R10.1, U1.31 (SIM_CLK)
SIM_DATA: C18.2, R11.1, U1.30 (SIM_DATA)
SIM_DET: J2.6 (VPP), R12.2, U1.33 (SIM_DET), U4.5
SIM_PWRKEY: J4.8, U1.8 (PWRKEY), U2.46 (PB9)
SIM_RST: J4.5, R9.1, U1.16 (~RESET), U1.32 (SIM_RST), U2.36 (PF7)
SIM_RX: J4.6, U1.15 (RXD), U2.30 (PA9)
SIM_TX: J4.7, U1.14 (TXD), U2.31 (PA10)
SIM_VDD: C17.2, J2.1 (VCC), U1.29 (SIM_VDD), U4.6
STATUS: U1.49 (STATUS), U2.2 (PC13)
SWDCLK: J4.4, U2.37 (PA14)
SWDIO: J4.2, U2.34 (PA13)
UART2_RX: U2.13 (PA3)
UART2_TX: U2.12 (PA2)
UART_RX: J3.6
UART_TX: J3.7

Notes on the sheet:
SIM HOLDER
ANTENNAS
Power filtering cct.
SIM808
Mounting Hole Pads
Decoupling circuit
POWER SUPPLY SYSTEM
STM32

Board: 2 copper layers, 59 parts (0 on the bottom side), 42 nets, no tracks yet.

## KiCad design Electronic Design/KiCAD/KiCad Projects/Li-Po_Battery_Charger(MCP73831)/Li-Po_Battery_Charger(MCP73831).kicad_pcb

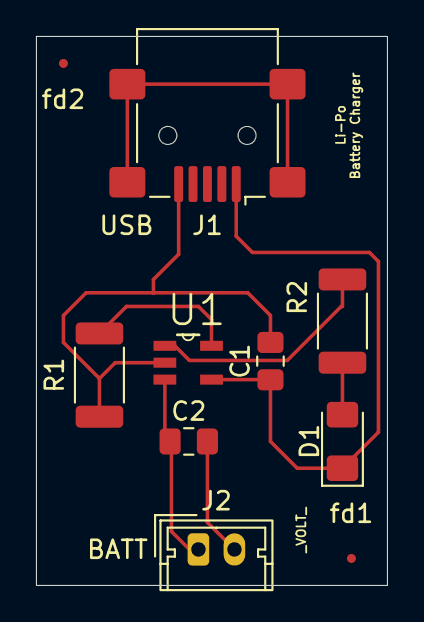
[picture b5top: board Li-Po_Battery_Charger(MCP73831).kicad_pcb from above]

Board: 2 copper layers, 19.5 x 30.5 mm, 10 parts (0 on the bottom side), 7 nets.

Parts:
C1, C2: C; C_0805_2012Metric_Pad1.18x1.45mm_HandSolder
D1: LED; LED_1206_3216Metric_Pad1.42x1.75mm_HandSolder
J1: USB; USB_Mini-B_Lumberg_2486_01_Horizontal
J2: BATT; Molex_Micro-Latch_53253-0270_1x02_P2.00mm_Vertical
R1, R2: ERJB1CFR015U; R_2010_5025Metric
U1: MCP73831T-2ACI_OT; SOT95P280X145-5N
fd1, fd2: Fiducial_0.5mm_Mask1.5mm

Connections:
GND: C1.2, J1.5 (GND), R1.1, U1.2 (VSS)
unnamed: D1.2 (A), R2.1
unnamed: C1.1, D1.1 (K), J1.1 (VBUS), U1.4 (VDD)
unnamed: C2.2, J2.1
unnamed: C2.1, J2.2, U1.3 (VBAT)
unnamed: R1.2, U1.5 (PROG)
unnamed: R2.2, U1.1 (STAT)
